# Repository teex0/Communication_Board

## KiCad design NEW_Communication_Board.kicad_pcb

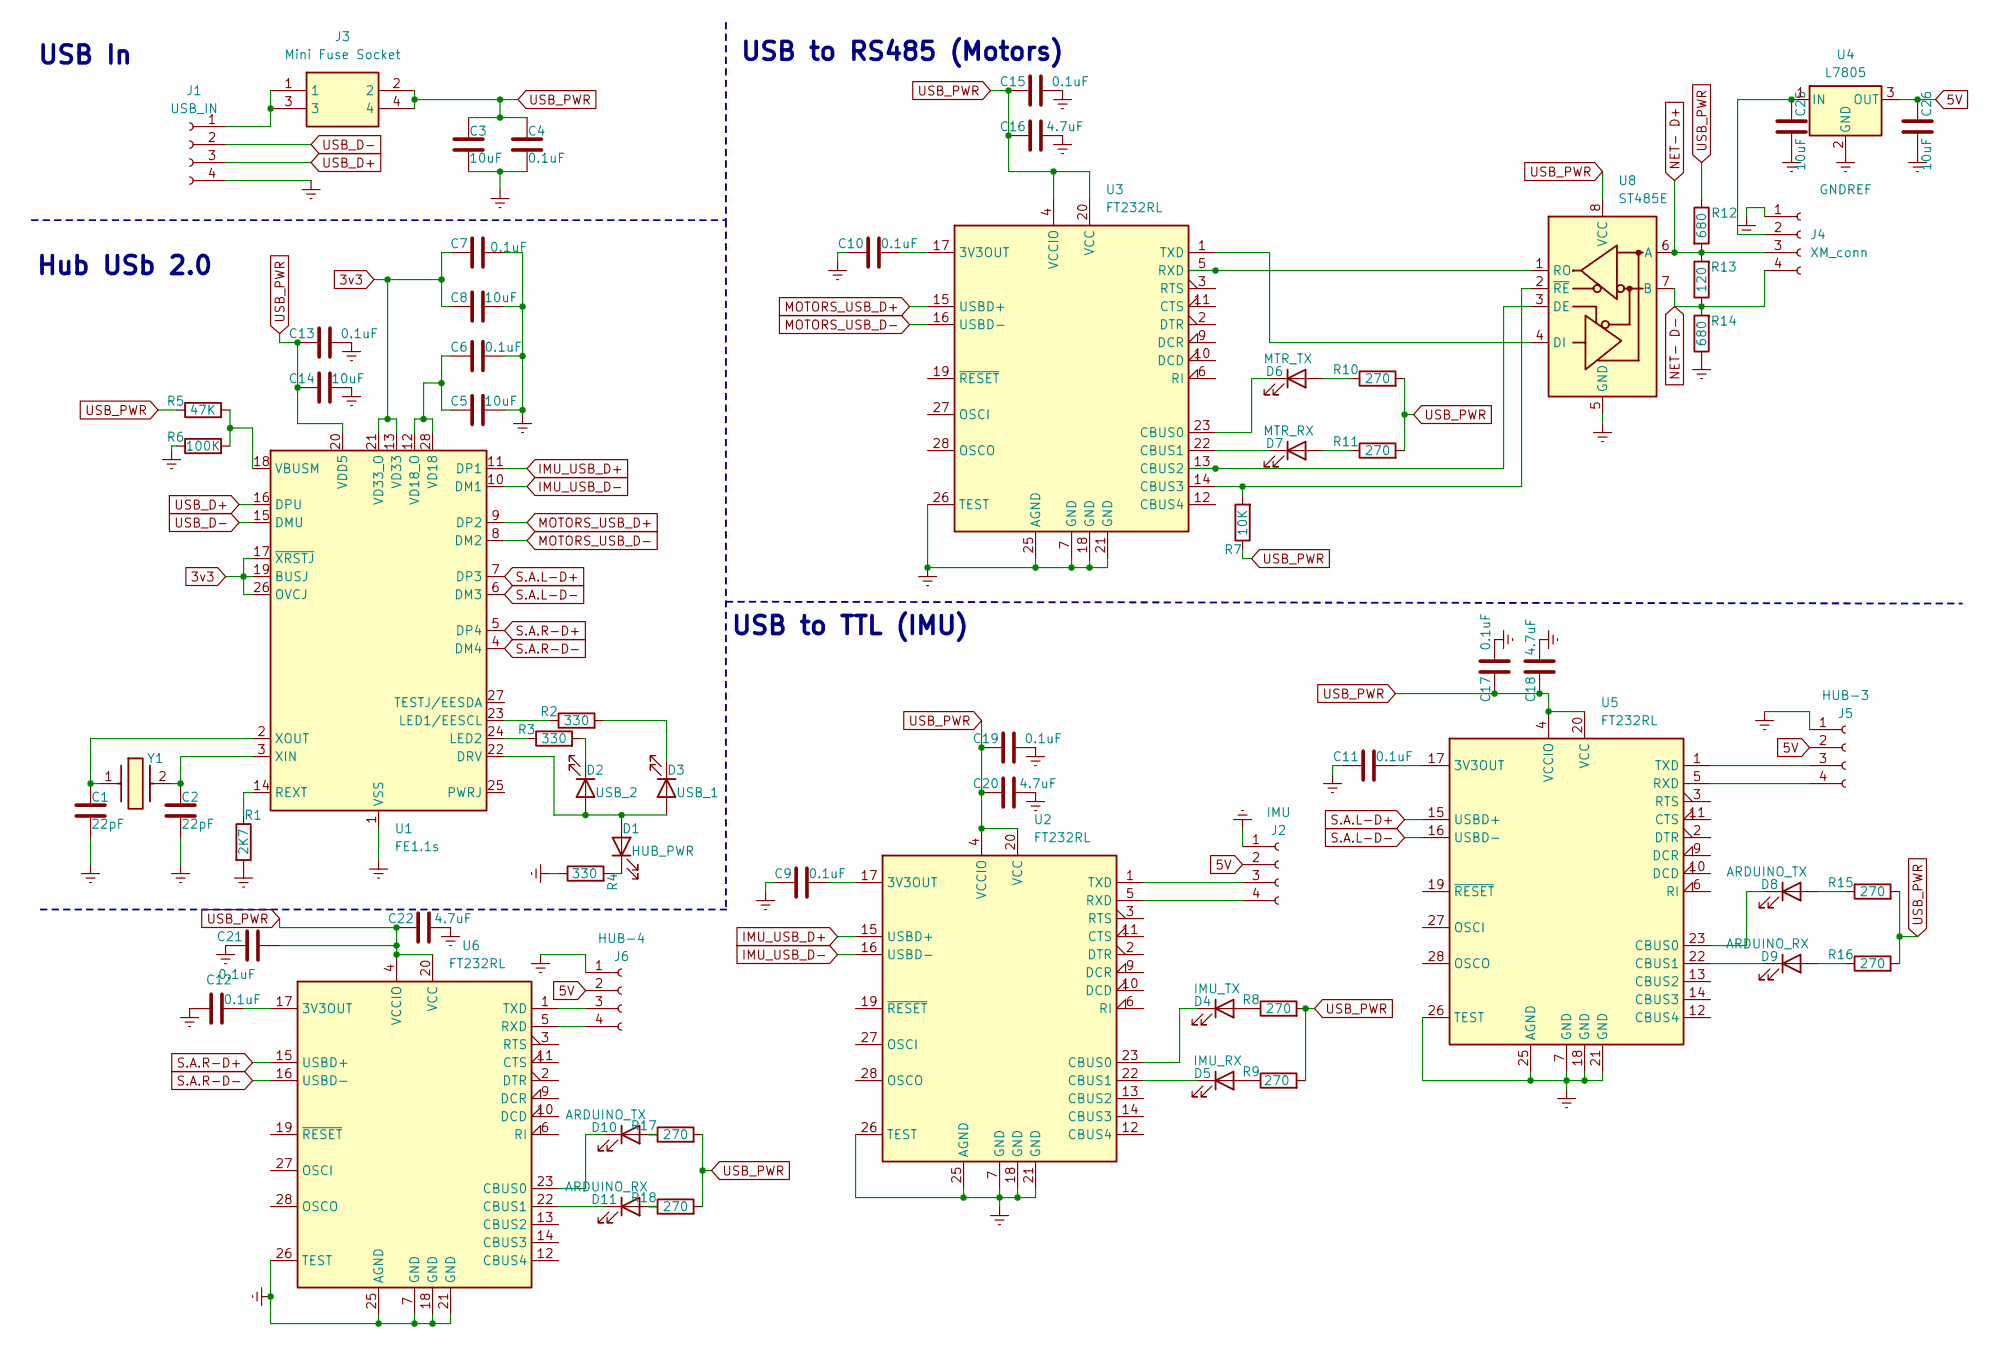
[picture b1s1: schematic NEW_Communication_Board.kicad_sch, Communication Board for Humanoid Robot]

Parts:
C1, C2: 22pF; C_1206_3216Metric
C3, C5, C8, C14, C25, C26: 10uF; C_1206_3216Metric
C4, C6, C7, C9, C10, C11, C12, C13, C15, C17, C19, C21: 0.1uF; C_1206_3216Metric
C16, C18, C20, C22: 4.7uF; C_1206_3216Metric
D1: HUB_PWR; LED_1206_3216Metric_Pad1.42x1.75mm_HandSolder
D2: USB_2; LED_1206_3216Metric_Pad1.42x1.75mm_HandSolder
D3: USB_1; LED_1206_3216Metric_Pad1.42x1.75mm_HandSolder
D4: IMU_TX; LED_1206_3216Metric_Pad1.42x1.75mm_HandSolder
D5: IMU_RX; LED_1206_3216Metric_Pad1.42x1.75mm_HandSolder
D6: MTR_TX; LED_1206_3216Metric_Pad1.42x1.75mm_HandSolder
D7: MTR_RX; LED_1206_3216Metric_Pad1.42x1.75mm_HandSolder
D8, D10: ARDUINO_TX; LED_1206_3216Metric_Pad1.42x1.75mm_HandSolder
D9, D11: ARDUINO_RX; LED_1206_3216Metric_Pad1.42x1.75mm_HandSolder
J1: USB_IN; PinHeader_1x04_P2.54mm_Vertical
J2: IMU; PinHeader_1x04_P2.54mm_Vertical
J3: Mini Fuse Socket; Mouser Part Number 534-3557-2
J4: XM_conn; XM_conn_vertical-B4B-EH-A
J5: HUB-3; PinHeader_1x04_P2.00mm_Vertical
J6: HUB-4; PinHeader_1x04_P2.00mm_Vertical
R1: 2K7; R_1206_3216Metric
R2, R3, R4: 330; R_1206_3216Metric
R5: 47K; R_1206_3216Metric
R6: 100K; R_1206_3216Metric
R7: 10K; R_1206_3216Metric
R8, R9, R10, R11, R15, R16, R17, R18: 270; R_1206_3216Metric
R12, R14: 680; R_1206_3216Metric
R13: 120; R_1206_3216Metric
U1: FE1.1s; SSOP-28_3.9x9.9mm_P0.635mm
U2, U3, U5, U6: FT232RL; SSOP-28_5.3x10.2mm_P0.65mm
U4: L7805; TO-252-2
U8: ST485E; SOIC-8_3.9x4.9mm_P1.27mm
Y1: Crystal 12MHz - ECS; Mouser Part Number 520-120-18-5PX-GM-TR

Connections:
3v3: C7.1, C8.1, U1.13 (VD33), U1.17 (~XRSTJ), U1.19 (BUSJ), U1.21 (VD33_O), U1.26 (OVCJ)
5V: C26.1, J2.2, J5.2, J6.2, U4.3 (OUT)
GNDREF: C1.2, C2.2, C3.2, C4.2, C5.2, C6.2, C7.2, C8.2, C9.1, C10.1, C11.1, C12.1, C13.2, C14.2, C15.2, C16.2, C17.2, C18.2, C19.2, C20.2, C21.1, C22.2, C25.2, C26.2, J1.4, J2.1, J4.1 (GND), J5.1, J6.1, R1.2, R4.1, R6.1, R14.1, U1.1 (VSS), U2.7 (GND), U2.18 (GND), U2.21 (GND), U2.25 (AGND), U2.26 (TEST), U3.7 (GND), U3.18 (GND), U3.21 (GND), U3.25 (AGND), U3.26 (TEST), U4.2 (GND), U5.7 (GND), U5.18 (GND), U5.21 (GND), U5.25 (AGND), U5.26 (TEST), U6.7 (GND), U6.18 (GND), U6.21 (GND), U6.25 (AGND), U6.26 (TEST), U8.5 (GND)
IMU_USB_D+: U1.11 (DP1), U2.15 (USBD+)
IMU_USB_D-: U1.10 (DM1), U2.16 (USBD-)
MOTORS_USB_D+: U1.9 (DP2), U3.15 (USBD+)
MOTORS_USB_D-: U1.8 (DM2), U3.16 (USBD-)
NET- D+: J4.3 (D+), R12.2, R13.2, U8.6 (A)
NET- D-: J4.4 (D-), R13.1, R14.2, U8.7 (B)
unnamed: D1.2 (A), D2.2 (A), D3.2 (A), U1.22 (DRV)
unnamed: D1.1 (K), R4.2
unnamed: D2.1 (K), R3.2
unnamed: D3.1 (K), R2.2
unnamed: D4.2 (A), R8.1
unnamed: D4.1 (K), U2.23 (CBUS0)
unnamed: D5.2 (A), R9.1
unnamed: D5.1 (K), U2.22 (CBUS1)
unnamed: D6.2 (A), R10.1
unnamed: D6.1 (K), U3.23 (CBUS0)
unnamed: D7.2 (A), R11.1
unnamed: D7.1 (K), U3.22 (CBUS1)
unnamed: D8.2 (A), R15.1
unnamed: D8.1 (K), U5.23 (CBUS0)
unnamed: D9.2 (A), R16.1
unnamed: D9.1 (K), U5.22 (CBUS1)
unnamed: D10.2 (A), R17.1
unnamed: D10.1 (K), U6.23 (CBUS0)
unnamed: D11.2 (A), R18.1
unnamed: D11.1 (K), U6.22 (CBUS1)
unnamed: J1.1, J3.1, J3.3
unnamed: J2.3, U2.1 (TXD)
unnamed: J2.4, U2.5 (RXD)
unnamed: C25.1, J4.2 (VDD), U4.1 (IN)
unnamed: J5.3, U5.1 (TXD)
unnamed: J5.4, U5.5 (RXD)
unnamed: J6.3, U6.1 (TXD)
unnamed: J6.4, U6.5 (RXD)
unnamed: R2.1, U1.23 (LED1/EESCL)
unnamed: R3.1, U1.24 (LED2)
unnamed: R1.1, U1.14 (REXT)
unnamed: R5.2, R6.2, U1.18 (VBUSM)
unnamed: C5.1, C6.1, U1.12 (VD18_O), U1.28 (VD18)
unnamed: C2.1, U1.3 (XIN), Y1.2
unnamed: C1.1, U1.2 (XOUT), Y1.1
unnamed: C9.2, U2.17 (3V3OUT)
unnamed: C10.2, U3.17 (3V3OUT)
unnamed: U3.13 (CBUS2), U8.3 (DE)
unnamed: R7.2, U3.14 (CBUS3), U8.2 (~RE)
unnamed: U3.5 (RXD), U8.1 (RO)
unnamed: U3.1 (TXD), U8.4 (DI)
unnamed: C11.2, U5.17 (3V3OUT)
unnamed: C12.2, U6.17 (3V3OUT)
S.A.L-D+: U1.7 (DP3), U5.15 (USBD+)
S.A.L-D-: U1.6 (DM3), U5.16 (USBD-)
S.A.R-D+: U1.5 (DP4), U6.15 (USBD+)
S.A.R-D-: U1.4 (DM4), U6.16 (USBD-)
USB_D+: J1.3, U1.16 (DPU)
USB_D-: J1.2, U1.15 (DMU)
USB_PWR: C3.1, C4.1, C13.1, C14.1, C15.1, C16.1, C17.1, C18.1, C19.1, C20.1, C21.2, C22.1, J3.2, J3.4, R5.1, R7.1, R8.2, R9.2, R10.2, R11.2, R12.1, R15.2, R16.2, R17.2, R18.2, U1.20 (VDD5), U2.4 (VCCIO), U2.20 (VCC), U3.4 (VCCIO), U3.20 (VCC), U5.4 (VCCIO), U5.20 (VCC), U6.4 (VCCIO), U6.20 (VCC), U8.8 (VCC)

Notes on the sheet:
USB In
USB to RS485 (Motors)
Hub USb 2.0
USB to TTL (IMU)

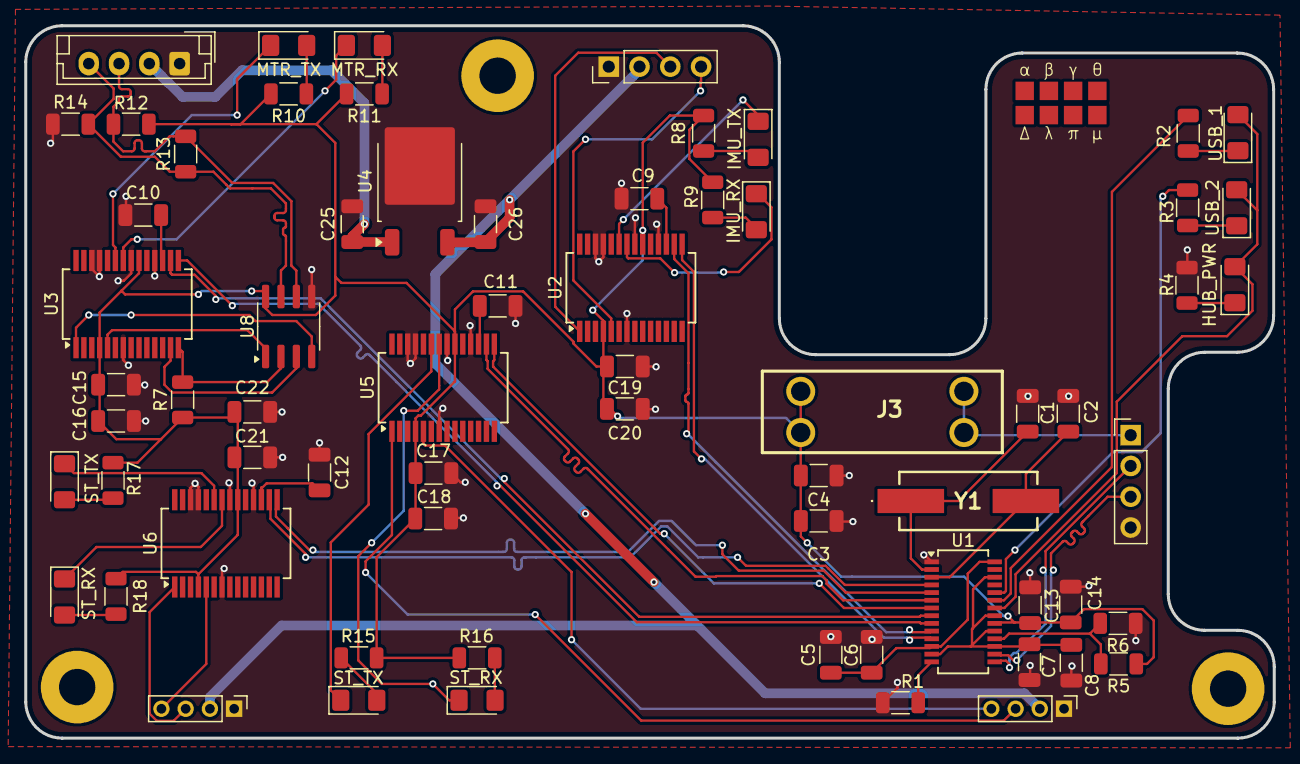
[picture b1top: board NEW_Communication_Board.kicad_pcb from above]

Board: 4 copper layers, 103.0 x 58.8 mm, 67 parts (0 on the bottom side), 59 nets.
